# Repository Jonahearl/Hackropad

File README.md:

# Hackropad

I have tried to create a macropad which will allow me to do some fun things especially with what i'm hoping will work like arrow keys.

This is my first ever PCB
I also just realised I don't actually know how to code in python so whatever I do probably won't even work haha

# Specifications
BOM
- 10x Cherry MX Switches
- 14x SK6812 MINI Leds
- 1x XIAO RP2040
- 10x Blank DSA Keycaps
- 4x M3x16 Bolt
- 4x M3 Heatset

Others:
- KMK Firmware
- Cover.step
- Base.step

# Schematic image

# PCB image

# Cad images

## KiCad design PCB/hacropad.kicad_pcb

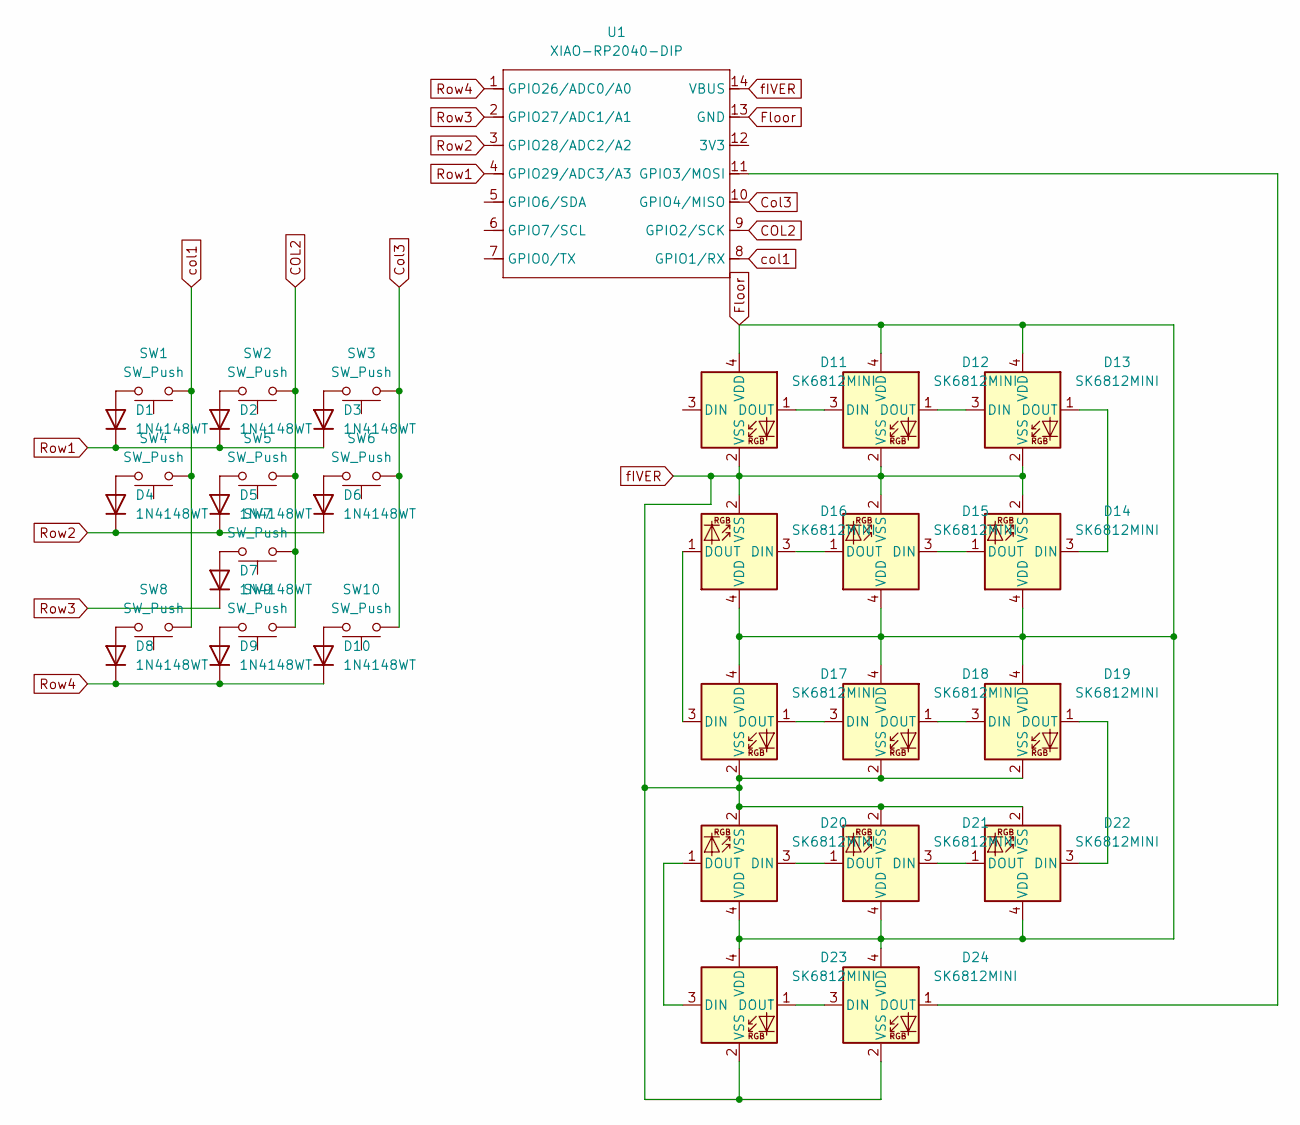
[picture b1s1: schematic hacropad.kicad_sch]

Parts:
D1, D2, D3, D4, D5, D6, D7, D8, D9, D10: 1N4148WT; D_SOD-523
D11, D12, D13, D14, D15, D16, D17, D18, D19, D20, D21, D22, D23, D24: SK6812MINI; LED_SK6812MINI_PLCC4_3.5x3.5mm_P1.75mm
SW1, SW2, SW3, SW4, SW5, SW6, SW7, SW8, SW9, SW10: SW_Push; SW_Cherry_MX_1.00u_PCB
U1: XIAO-RP2040-DIP

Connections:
COL2: SW2.1, SW5.1, SW7.1, SW9.1, U1.9 (GPIO2/SCK)
Col3: SW3.1, SW6.1, SW10.1, U1.10 (GPIO4/MISO)
Floor: D11.4 (VDD), D12.4 (VDD), D13.4 (VDD), D14.4 (VDD), D15.4 (VDD), D16.4 (VDD), D17.4 (VDD), D18.4 (VDD), D19.4 (VDD), D20.4 (VDD), D21.4 (VDD), D22.4 (VDD), D23.4 (VDD), D24.4 (VDD), U1.13 (GND)
unnamed: D1.2 (A), SW1.2
unnamed: D2.2 (A), SW2.2
unnamed: D3.2 (A), SW3.2
unnamed: D4.2 (A), SW4.2
unnamed: D5.2 (A), SW5.2
unnamed: D6.2 (A), SW6.2
unnamed: D7.2 (A), SW7.2
unnamed: D8.2 (A), SW8.2
unnamed: D9.2 (A), SW9.2
unnamed: D10.2 (A), SW10.2
unnamed: D11.1 (DOUT), D12.3 (DIN)
unnamed: D12.1 (DOUT), D13.3 (DIN)
unnamed: D13.1 (DOUT), D14.3 (DIN)
unnamed: D14.1 (DOUT), D15.3 (DIN)
unnamed: D15.1 (DOUT), D16.3 (DIN)
unnamed: D16.1 (DOUT), D17.3 (DIN)
unnamed: D17.1 (DOUT), D18.3 (DIN)
unnamed: D18.1 (DOUT), D19.3 (DIN)
unnamed: D19.1 (DOUT), D22.3 (DIN)
unnamed: D20.3 (DIN), D21.1 (DOUT)
unnamed: D20.1 (DOUT), D23.3 (DIN)
unnamed: D21.3 (DIN), D22.1 (DOUT)
unnamed: D23.1 (DOUT), D24.3 (DIN)
unnamed: D24.1 (DOUT), U1.11 (GPIO3/MOSI)
Row1: D1.1 (K), D2.1 (K), D3.1 (K), U1.4 (GPIO29/ADC3/A3)
Row2: D4.1 (K), D5.1 (K), D6.1 (K), U1.3 (GPIO28/ADC2/A2)
Row3: D7.1 (K), U1.2 (GPIO27/ADC1/A1)
Row4: D8.1 (K), D9.1 (K), D10.1 (K), U1.1 (GPIO26/ADC0/A0)
col1: SW1.1, SW4.1, SW8.1, U1.8 (GPIO1/RX)
fIVER: D11.2 (VSS), D12.2 (VSS), D13.2 (VSS), D14.2 (VSS), D15.2 (VSS), D16.2 (VSS), D17.2 (VSS), D18.2 (VSS), D19.2 (VSS), D20.2 (VSS), D21.2 (VSS), D22.2 (VSS), D23.2 (VSS), D24.2 (VSS), U1.14 (VBUS)

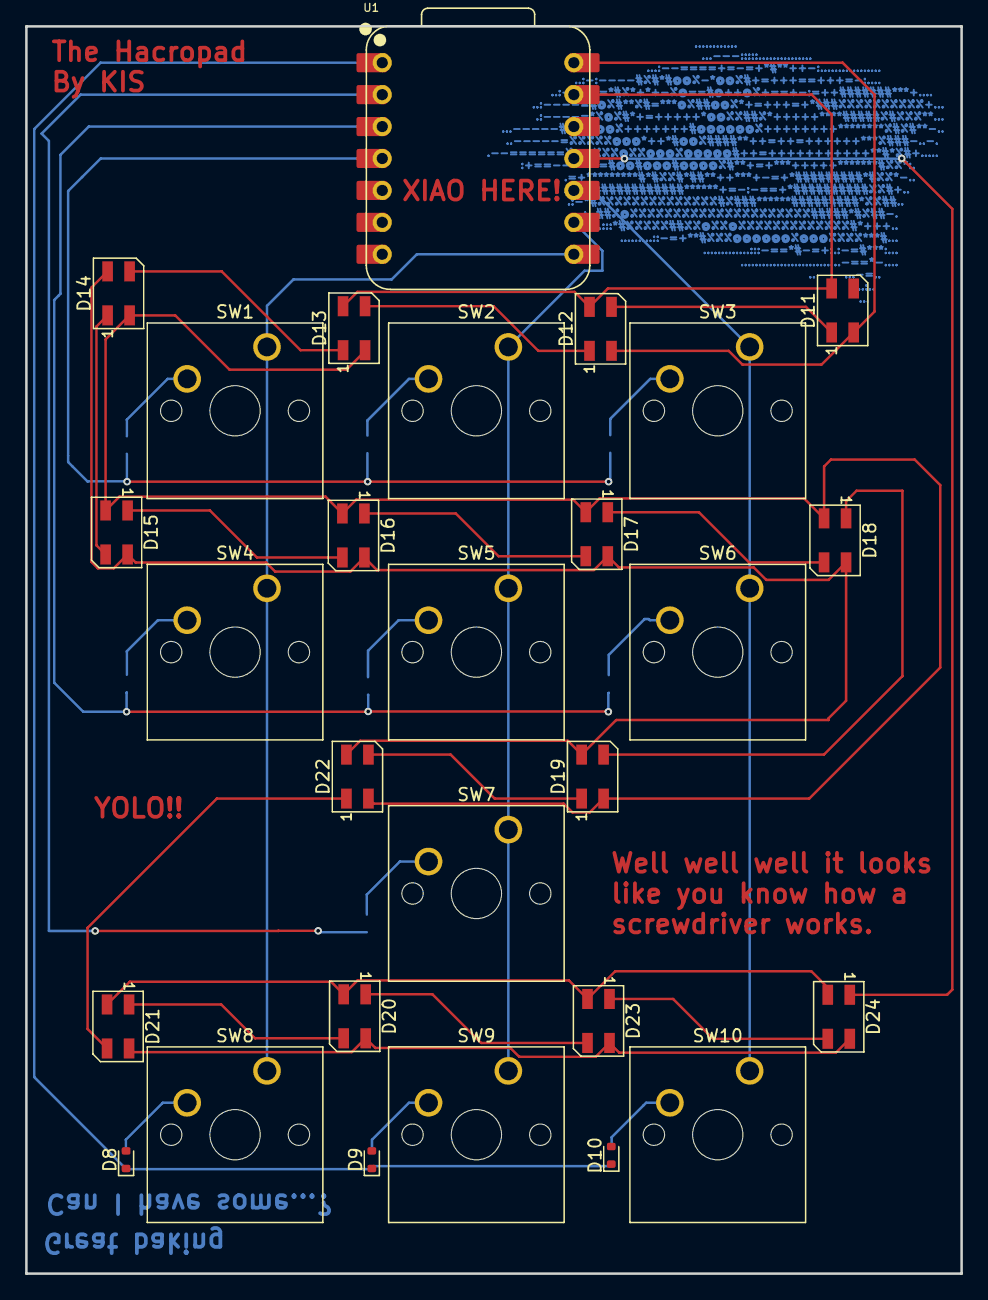
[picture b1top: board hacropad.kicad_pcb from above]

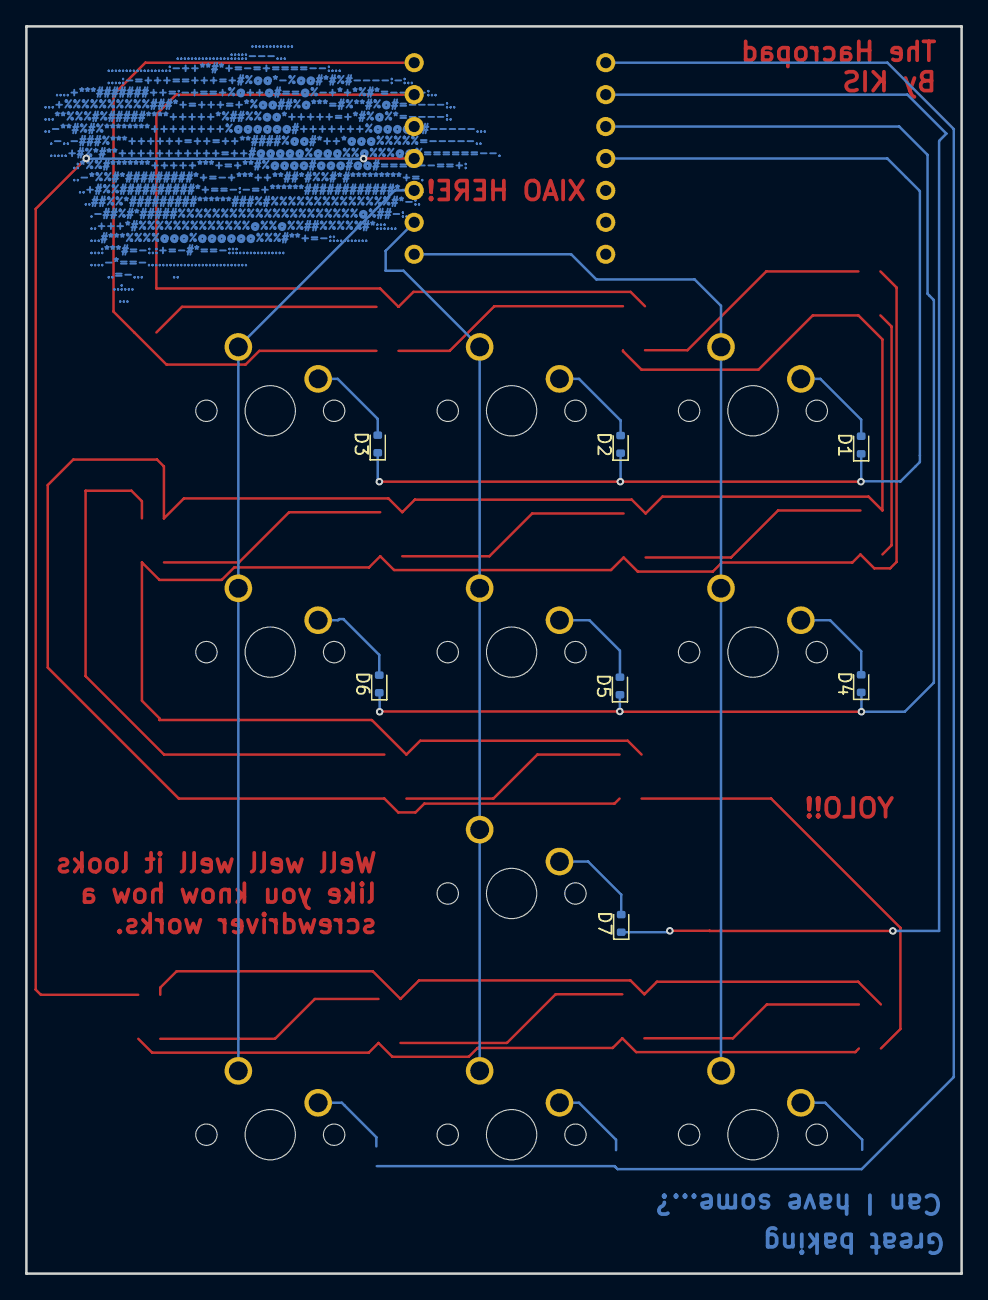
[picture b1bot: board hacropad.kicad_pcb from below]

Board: 2 copper layers, 74.4 x 99.2 mm, 35 parts (7 on the bottom side), 33 nets.

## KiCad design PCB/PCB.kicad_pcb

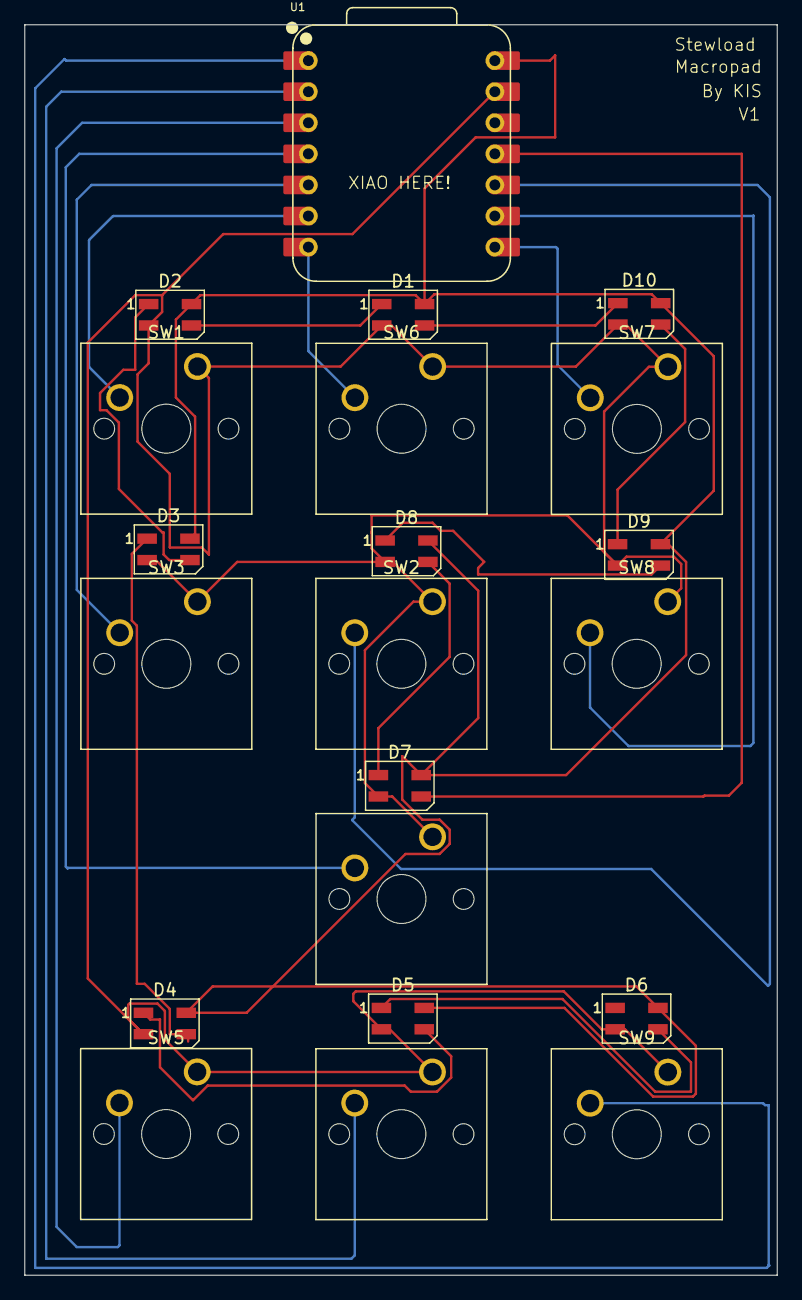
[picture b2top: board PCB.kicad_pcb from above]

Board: 2 copper layers, 61.5 x 102.2 mm, 21 parts (0 on the bottom side), 21 nets.

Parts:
D1, D2, D3, D4, D5, D6, D7, D8, D9, D10: SK6812MINI; LED_SK6812MINI_PLCC4_3.5x3.5mm_P1.75mm
SW1, SW2, SW3, SW4, SW5, SW6, SW7, SW8, SW9, SW10: SW_Push; SW_Cherry_MX_1.00u_PCB
U1: XIAO-RP2040-DIP

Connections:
unnamed: D1.3 (DIN), D10.1 (DOUT)
unnamed: D1.1 (DOUT), D2.3 (DIN)
unnamed: D1.4 (VDD), D2.4 (VDD), D3.4 (VDD), D4.4 (VDD), D5.4 (VDD), D6.4 (VDD), D7.4 (VDD), D8.4 (VDD), D9.4 (VDD), D10.4 (VDD), U1.14 (VBUS)
unnamed: D1.2 (VSS), D2.2 (VSS), D3.2 (VSS), D4.2 (VSS), D5.2 (VSS), D6.2 (VSS), D7.2 (VSS), D8.2 (VSS), D9.2 (VSS), D10.2 (VSS), SW1.1, SW2.1, SW3.1, SW4.1, SW5.1, SW6.1, SW7.1, SW8.1, SW9.1, SW10.1, U1.13 (GND)
unnamed: D2.1 (DOUT), D3.3 (DIN)
unnamed: D3.1 (DOUT), D4.3 (DIN)
unnamed: D4.1 (DOUT), D5.3 (DIN)
unnamed: D5.1 (DOUT), D6.3 (DIN), D7.3 (DIN), U1.11 (GPIO3/MOSI)
unnamed: D7.1 (DOUT), D8.3 (DIN)
unnamed: D8.1 (DOUT), D9.3 (DIN)
unnamed: D9.1 (DOUT), D10.3 (DIN)
unnamed: SW6.2, U1.7 (GPIO0/TX)
unnamed: SW7.2, U1.8 (GPIO1/RX)
unnamed: SW8.2, U1.9 (GPIO2/SCK)
unnamed: SW2.2, U1.10 (GPIO4/MISO)
unnamed: SW3.2, U1.5 (GPIO6/SDA)
unnamed: SW1.2, U1.6 (GPIO7/SCL)
unnamed: SW9.2, U1.1 (GPIO26/ADC0/A0)
unnamed: SW10.2, U1.2 (GPIO27/ADC1/A1)
unnamed: SW5.2, U1.3 (GPIO28/ADC2/A2)
unnamed: SW4.2, U1.4 (GPIO29/ADC3/A3)

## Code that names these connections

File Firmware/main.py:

#I do not know what the heck I am doing so we'll see if this works
import board
#I did in fact Borrow the basis or really most of this from the Cyao example...
from kmk.kmk_keyboard import KMKKeyboard
from kmk.keys import KC
from kmk.scanners import DiodeOrientation
from kmk.modules.macros import Macros
from kmk.extensions.display import Display, TextEntry
from kmk.extensions.LED import LED, AnimationModes
from kmk.extensions.display.ssd1306 import SSD1306

COL0 = board.GP7;
COL1 = board.GP8;
COL2 = board.GP9;
ROW0 = board.GP3;
ROW1 = board.GP2;
ROW2 = board.GP1;
ROW3 = board.GP0;

LED_PIN = board.GP10;

keyboard = KMKKeyboard();

macros = Macros();
keyboard.modules.append(macros);

keyboard.extensions.append(display);

led = LED(
    led_pin=[LED_PIN],
    animation_mode=AnimationModes.BREATHING,
    brightness=50
);
keyboard.extensions.append(led);

keyboard.col_pins = (COL0, COL1, COL2,);
keyboard.row_pins = (ROW0, ROW1, ROW2, ROW3);
keyboard.diode_orientation = DiodeOrientation.COL2ROW;

keyboard.keymap = [
    [KC.ESCAPE,      KC.ANY,   KC.ANY,  ],
    [KC.ANY,      KC.ANY,     KC.ANY,   ],
    [KC.TRNS,      KC.UP,     KC.TRNS,  ],
    [KC.LEFT,   KC.DOWN,   KC.RIGHT     ],
];

if __name__ == '__main__':
    keyboard.go();

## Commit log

2025-12-02 Create Cad files
2025-12-02 Remove CAD directory
2025-12-02 Create pla
2025-12-02 Enhance README with project details and images
    Added detailed project description and specifications.
2025-12-02 PYTHON?
2025-12-04 Create kl
2025-12-04 firm
2025-12-04 thefiler
2025-12-04 Update README with titles woah
    Added specifications, schematic, PCB, and CAD images.
2025-12-04 Edits
2025-12-04 More LED's?
2025-12-04 I used the wrong image
